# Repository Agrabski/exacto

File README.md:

Exacto
======

Rust project for the _Arduino Nano_, powering a reflex sight for airsoft guns with an integrated ballistic computer.

## Build Instructions
1. Install prerequisites as described in the [`avr-hal` README] (`avr-gcc`, `avr-libc`, `avrdude`, [`ravedude`]).

2. Run `cargo build` to build the firmware.

3. Run `cargo run` to flash the firmware to a connected board.  If `ravedude`
   fails to detect your board, check its documentation at
   <https://crates.io/crates/ravedude>.

4. `ravedude` will open a console session after flashing where you can interact
   with the UART console of your board.

[`avr-hal` README]: https://github.com/Rahix/avr-hal#readme
[`ravedude`]: https://crates.io/crates/ravedude

## License
Licensed under the GNU General Public License, Version 3 or (at your option)
any later version ([LICENSE](LICENSE) or <https://www.gnu.org/licenses/gpl-3.0.html>).

## Contribution
Unless you explicitly state otherwise, any contribution intentionally submitted
for inclusion in the work by you shall be licensed under the GPL-3.0 license,
without any additional terms or conditions.

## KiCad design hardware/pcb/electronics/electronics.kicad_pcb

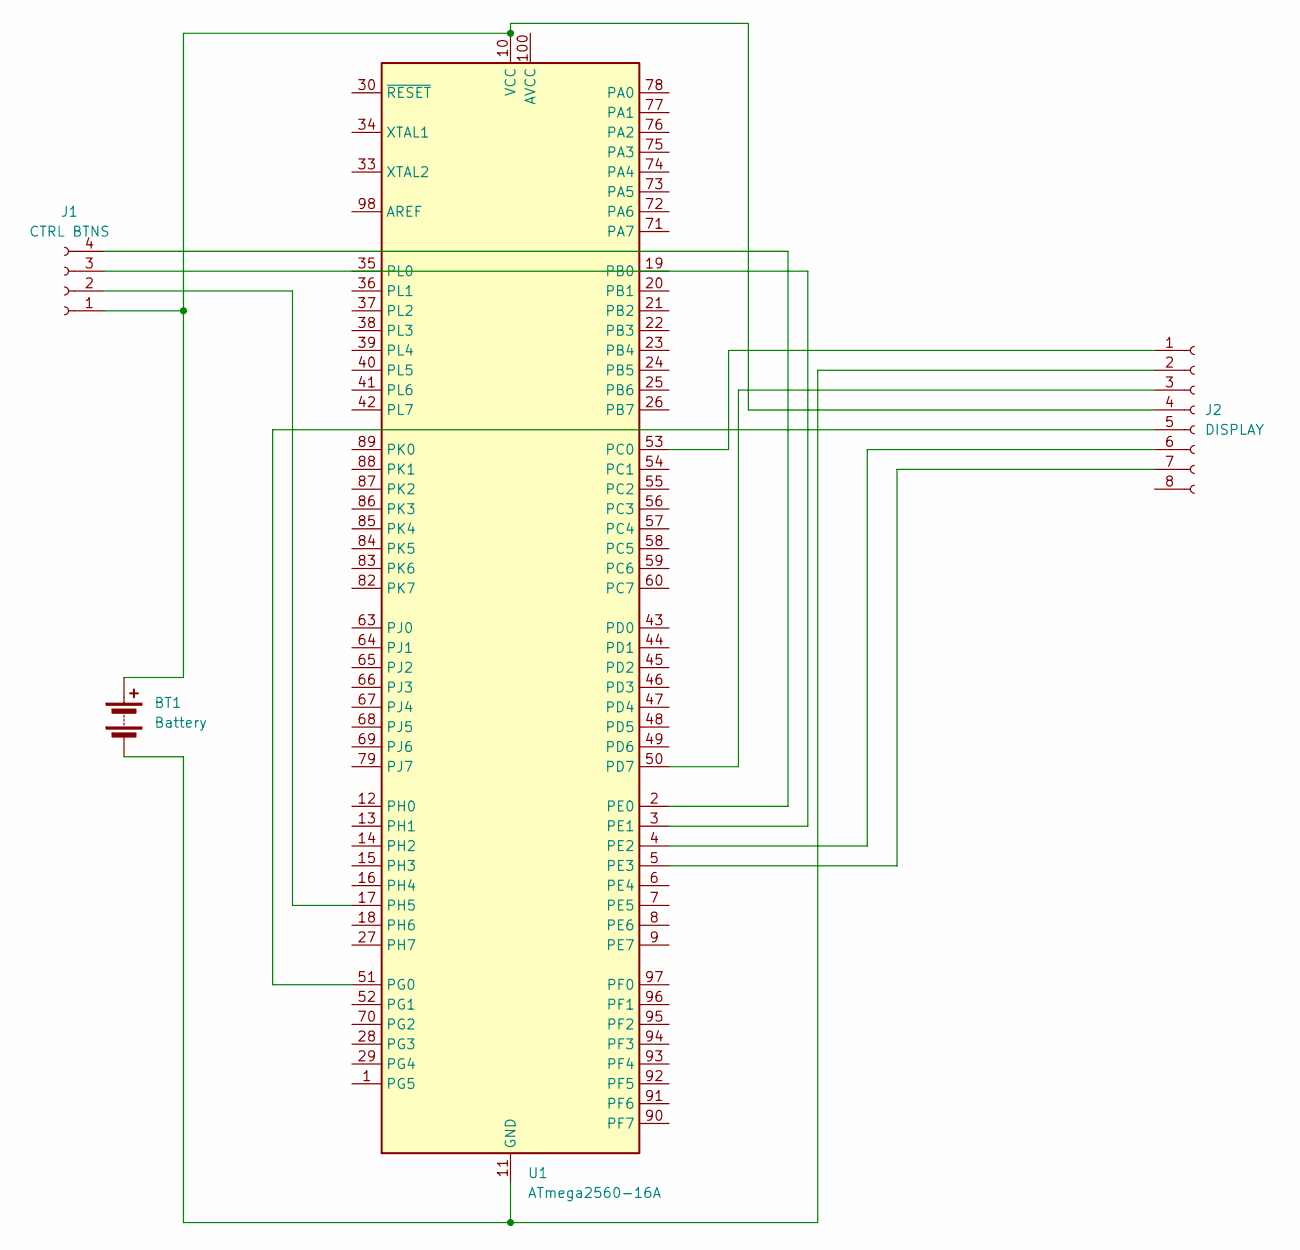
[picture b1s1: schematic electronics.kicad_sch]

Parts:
BT1: Battery; JWT_A3963_1x02_P3.96mm_Vertical
J1: CTRL BTNS; JST_EH_S4B-EH_1x04_P2.50mm_Horizontal
J2: DISPLAY; JST_EH_S8B-EH_1x08_P2.50mm_Horizontal
U1: ATmega2560-16A; TQFP-100_14x14mm_P0.5mm

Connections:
unnamed: BT1.1 (+), J1.1, J2.4, U1.10 (VCC), U1.31 (VCC), U1.61 (VCC), U1.80 (VCC)
unnamed: BT1.2 (-), J2.2, U1.11 (GND), U1.32 (GND), U1.62 (GND), U1.81 (GND), U1.99 (GND)
unnamed: J1.2, U1.17 (PH5)
unnamed: J1.3, U1.3 (PE1)
unnamed: J1.4, U1.2 (PE0)
unnamed: J2.1, U1.53 (PC0)
unnamed: J2.3, U1.50 (PD7)
unnamed: J2.5, U1.51 (PG0)
unnamed: J2.6, U1.4 (PE2)
unnamed: J2.7, U1.5 (PE3)

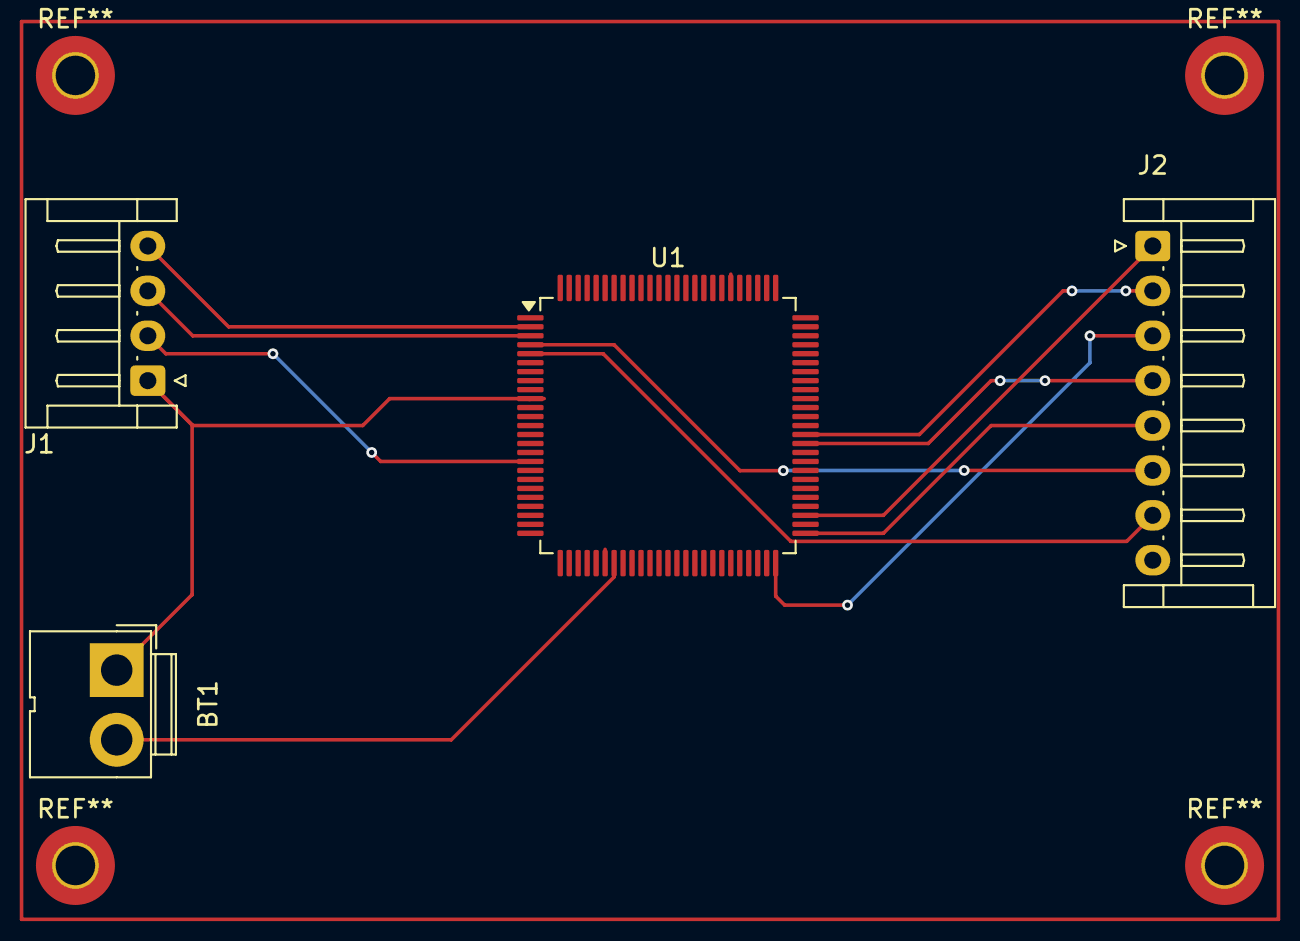
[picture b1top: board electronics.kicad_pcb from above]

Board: 2 copper layers, 4 parts (0 on the bottom side), 10 nets.

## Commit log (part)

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2025-06-10 initial
2025-06-11 display actuall works
2025-06-11 cleanup
2025-06-11 implement sight struct and display functionality
2025-06-12 switched rst and dc pins to free up interrupt pins
2025-06-12 refactor: update display initialization and add rotary encoder implementation
2025-06-16 first settings prototype
2025-06-19 settings menu rewrite
2025-06-19 sight menu
2025-06-20 transforms work
2025-06-20 adjusted colors
2025-06-20 Refactor settings menu and add slider functionality
2025-06-21 Add Y slider to SightMenu and update control references
2025-06-27 display h older sketch complete
2025-06-27 display holder finalised
2025-06-27 added lense graphic, started lense holder sketch
2025-06-28 finalised increment 0 CAD design
2025-06-28 Refactor reticle drawing logic to use center-based positioning
2025-06-29 Add ballistic calculator and physics modules with SI unit support
2025-07-02 doesnt flash...
2025-07-04 removed physical units
2025-07-04 debloating
2025-07-04 can flash, doesnt work
2025-07-05 split into crates
2025-07-06 fraction tests work
2025-07-06 fixed a bunch of stuff
2025-07-08 ballistic computer does not crash in tests. Not flashed yet
2025-07-09 firmware flashes and does not crash
2025-07-13 started designing the scope body from scratch
2026-05-27 Add OpenSCAD sight housing with adjustable screen-to-lens angle
    Parametric model for 3D printing the reflex sight housing.
    Dimensions taken from hardware/display/dimensions.png (42.20x29.00mm PCB,
    38.00x24.80mm active area). Lens arm pivots on an M3 hinge pin; an arc
    slot (30-60°, 5° detents) and lock bolt let the screen-to-lens angle be
    set at print time or adjusted after assembly.
    https://claude.ai/code/session_01CGtrs7Z3cyJTER9gnwPHDv
2026-05-27 Simplify sight housing: fixed angle set at design time, no hinge
    Replaced the hinge + arc-slot mechanism with a single `angle` parameter.
    The arm and body are one solid printed piece; change the parameter,
    re-export the STL, and reprint to get a different angle.
    https://claude.ai/code/session_01CGtrs7Z3cyJTER9gnwPHDv
2026-05-27 Update lens dimensions from hardware/lens/lense.avif
    Collimating lens: 24×34 mm, 2.74 mm thick, R16.97 rounded top arc.
    Lens frame profile now matches the actual lens shape (rectangular body
    + rounded hull cap). Frame pocket uses lens_top_r for the arc slot.
    https://claude.ai/code/session_01CGtrs7Z3cyJTER9gnwPHDv
2026-05-27 Add render-cad and 3d-model subagent definitions
    render-cad: generates matplotlib renders of the sight housing from
    the SCAD geometry, with correct arm transform math and lens arc formula.
    3d-model: maintains the OpenSCAD file with authoritative dimension
    tables, lens profile geometry derivation (rect_h = 29.03 mm),
    and coordinate system notes.
    https://claude.ai/code/session_01CGtrs7Z3cyJTER9gnwPHDv
2026-05-27 Redesign sight housing: two-post bracket with correct glass geometry
    Replace the diagonal rib arm with a proper reflex sight architecture:
    - rear_post(): tall wall (Y=0) that supports the high edge of the glass
    - front_post(): short ledge (Y=body_d) for the low edge
    - side_rails(): sloped walls connecting the two posts, top edge follows
    the glass tilt angle
    - glass_frame_mount(): lens frame rotated with rotate([90-angle,0,0]) so
2026-05-27 Fix lens_frame() arc cap: clip cylinder to sliver above outer_rect_h
    Full 360° cylinder was making the frame look circular. Now uses
    intersection() to keep only the ~6.5 mm sagitta above outer_rect_h
    (32.52 mm) for both the outer shell and the glass pocket, matching
    the actual flat-rectangular-with-small-arc-top lens profile.
    https://claude.ai/code/session_01CGtrs7Z3cyJTER9gnwPHDv
2026-05-27 Fix lens_frame() pocket: add bottom arc to match actual lens profile
    The lens has arcs on BOTH ends (R16.97, sag 4.97 mm), not just the top.
    The glass pocket previously had a flat-bottomed rectangle that didn't
    match the lens shape, so the lens would only contact the pocket at a
    single centre-bottom point with gaps at the sides.
    Changes:
    - Add bot_rect_z = lens_top_r - sqrt(R²-(w/2)²) = 4.97 mm to derived vars
2026-05-27 Add outer bottom arc to lens_frame() shell
    The outer frame profile now mirrors the lens shape on both ends:
    straight section between z=outer_bot_rect_z (6.48 mm) and
    outer_rect_h (32.52 mm), with arc caps (R=R_outer=19.47 mm) clipped
    above/below those tangent lines. Previously the outer shell had a flat
    bottom, making the frame silhouette inconsistent with the lens profile.
    https://claude.ai/code/session_01CGtrs7Z3cyJTER9gnwPHDv
2026-05-27 Redesign sight housing to EOTech-style window shroud
    Replace the two-post / side-rail bracket with an enclosed rectangular
    window frame (solid left/right walls, top hood bar, front/rear lower lips).
    The glass_frame_mount is unchanged — combiner glass still tilts at `angle`
    degrees and sits inside the shroud aperture.
    Removes: rear_post, front_post, side_rails modules
    Adds: eotech_shroud module with shroud_wall=3mm, lip_h=10mm
2026-05-27 Add OpenSCAD render script (hardware/cad/render.py)
    Drives openscad --render via xvfb-run from three camera angles and
    composites the result into a single PNG using matplotlib + Pillow.
    Replaces the hand-built matplotlib geometry approach with actual SCAD
    output (DeepOcean colour scheme, 900×700 per view).
    Usage: python hardware/cad/render.py [--out PATH]
    https://claude.ai/code/session_01CGtrs7Z3cyJTER9gnwPHDv
2026-06-04 Rotate lens to landscape orientation (34 mm horizontal, 24 mm along tilt)
    The physical arc radius (R=16.97 mm) can only span the 24 mm short edge
    (half-chord 12 mm < R). Placing 34 mm horizontal gives a 34×17 mm
    projected aperture at 45° — matching EOTech proportions — vs the previous
    portrait 24×24 mm square aperture.
    Changes:
    - arm_w = lens_h + 2×wall = 39 mm (was lens_w-based, 29 mm)
2026-06-13 Fix arc cap pocket bug: cylinder was centred at frame_y/2, blocking entry face
    The glass pocket arc cap cylinders were centred at Y=frame_y/2=3.87 mm,
    meaning the subtraction only started at Y=2.25 mm. The lens curved ends
    would hit solid material at the entry face (Y=0) and the glass could not
    be inserted. Fix: centre the cylinders at Y=(lens_t+clearance)/2=1.52 mm
    so the pocket spans Y≈0..lens_t+clearance at the arc cap regions,
    matching the straight-section pocket depth.
2026-06-13 Update render views: add front-aperture angle, improve isometrics
    Replaces the uninformative side-profile view with a front-aperture
    view (elev=20, azim=180) that shows the tilted glass inside the
    window opening. Adjusts front-left isometric elevation to 40°.
    https://claude.ai/code/session_01CGtrs7Z3cyJTER9gnwPHDv
2026-06-13 Add M2 set-screw retention holes to lens frame for glass assembly
    Two M2×4 set-screw holes (ø2.1 mm, 2.5 mm deep) through the left and
    right arc side walls of the lens frame. Screws bear on the glass arc
    edges, clamping the combiner glass via friction after insertion through
    the entry face. Enables non-destructive assembly and disassembly without
    adhesive.
    https://claude.ai/code/session_01CGtrs7Z3cyJTER9gnwPHDv
2026-06-13 Switch to optics-only body: remove USB port, fix PCB pocket clearance
    Electronics (MCU, battery, USB) are now external; the sight body
    houses only the OLED PCB. Changes to screen_body():
    - Remove USB/power port cutout from front wall
    - Add clearance/2 on each side of PCB pocket so PCB drops in freely
    - Update module comment to reflect external-electronics design
    https://claude.ai/code/session_01CGtrs7Z3cyJTER9gnwPHDv
2026-06-13 Add legacy matplotlib render script (pre-OpenSCAD fallback)
    Kept for reference; the canonical render is render.py (OpenSCAD-based).
    https://claude.ai/code/session_01CGtrs7Z3cyJTER9gnwPHDv
2026-06-13 Replace non-ASCII chars in lens_frame retention comments
    Substituted Unicode multiply sign and arrow with ASCII equivalents
    (x and comma) to avoid parser errors in older OpenSCAD builds.
    https://claude.ai/code/session_01CGtrs7Z3cyJTER9gnwPHDv
2026-06-13 Merge lens frame arms into shroud side walls
    Added rectangular arms in glass_frame_mount() that extend the lens
    frame from its natural width (arm_w=39mm) all the way through the
    shroud side walls to the body edges. The 4.1mm arms on each side
    close the gap between the floating frame and the walls, making the
    combiner mount a single merged solid with the housing.
    https://claude.ai/code/session_01CGtrs7Z3cyJTER9gnwPHDv
2026-06-15 fixed licensing
2026-06-16 ported to atmega 2850
2026-06-19 Replace single-element combiner lens with true birdbath optics
    Swap the tilted curved-meniscus combiner lens for a two-element birdbath:
    a flat 30/70 beamsplitter (1st bounce off the display) and a curved
    collimating mirror (2nd bounce back through the same beamsplitter panel
    to the eye). The fold geometry (mirror_tilt, mirror_R, hit-point
    positions) is fully derived from `angle` via closed-form 2D ray-trace
    formulas, verified to keep the exit ray perfectly level for any angle in
2026-06-19 hardened fraction
2026-06-19 birdbath design
2026-06-19 added removable optics pocket
2026-06-28 started pcb design
2026-06-30 balistic calculator basically works
